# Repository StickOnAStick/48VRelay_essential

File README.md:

Ignore me trying to work with ki-cads git management. Project is located at `RelatBoard/48VRelay/48VERelay`

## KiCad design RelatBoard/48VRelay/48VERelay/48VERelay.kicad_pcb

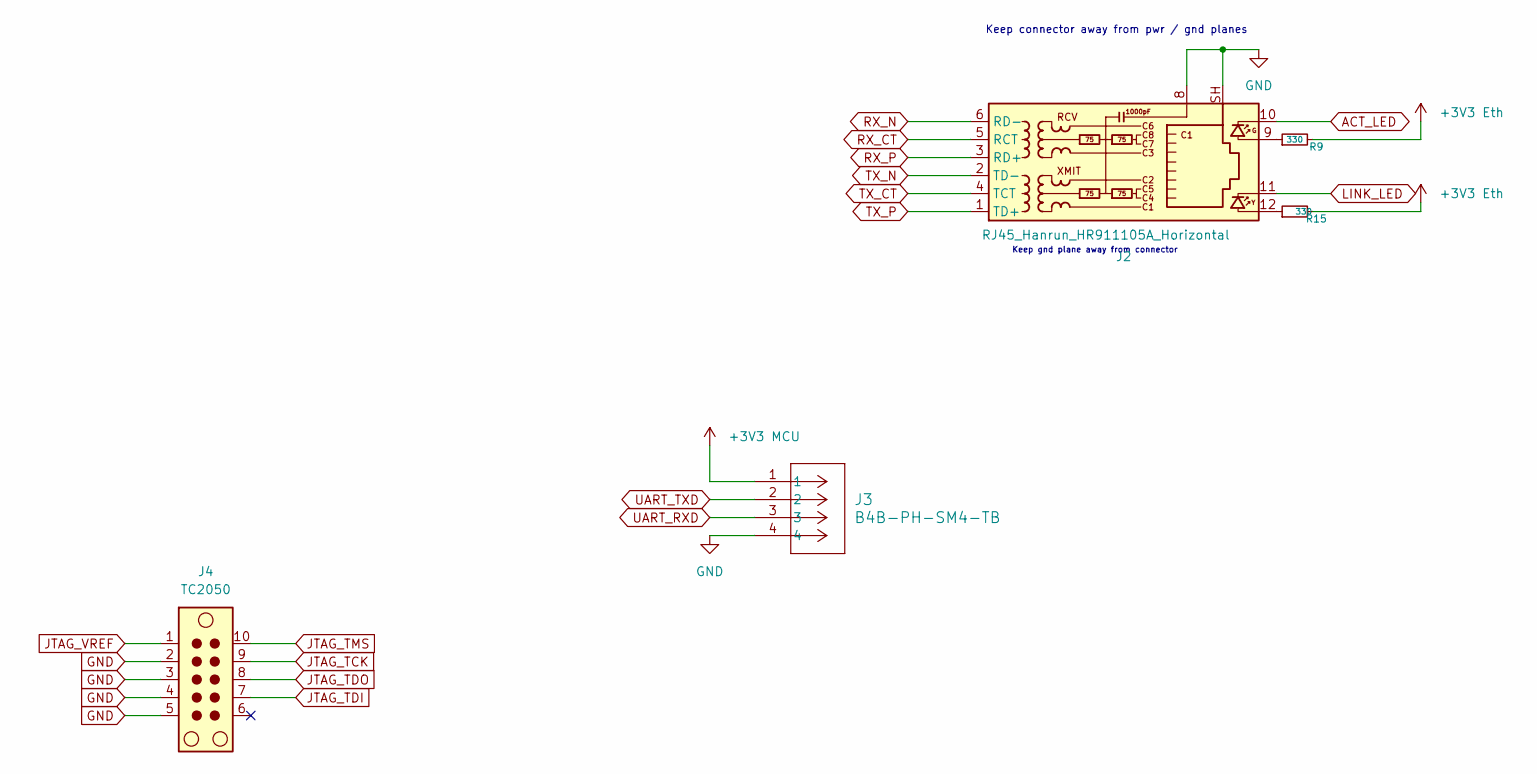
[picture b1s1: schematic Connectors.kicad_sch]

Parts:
J2: RJ45_Hanrun_HR911105A_Horizontal
J3: B4B-PH-SM4-TB; PinHeader_1x04_P2.54mm_Vertical
J4: TC2050; Tag-Connect_TC2050-IDC-NL_2x05_P1.27mm_Vertical
R9, R15: 330; R_0603_1608Metric

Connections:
3V3 MCU: J3.1, J4.1; also elsewhere on the board
+3V3 Eth: R9.2, R15.2; also elsewhere on the board
ACT_LED: J2.10; also elsewhere on the board
GND: J2.8, J2.SH, J3.4, J4.2, J4.3, J4.4, J4.5; also elsewhere on the board
JTAG_TCK: J4.9; also elsewhere on the board
JTAG_TDI: J4.7; also elsewhere on the board
JTAG_TDO: J4.8; also elsewhere on the board
JTAG_TMS: J4.10; also elsewhere on the board
LINK_LED: J2.11; also elsewhere on the board
unnamed: J2.9, R9.1
unnamed: J2.12, R15.1
RX_CT: J2.5 (RCT); also elsewhere on the board
RX_N: J2.6 (RD-); also elsewhere on the board
RX_P: J2.3 (RD+); also elsewhere on the board
TX_CT: J2.4 (TCT); also elsewhere on the board
TX_N: J2.2 (TD-); also elsewhere on the board
TX_P: J2.1 (TD+); also elsewhere on the board
UART_RXD: J3.3; also elsewhere on the board
UART_TXD: J3.2; also elsewhere on the board

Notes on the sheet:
Keep gnd plane away from connector
Keep connector away from pwr / gnd planes

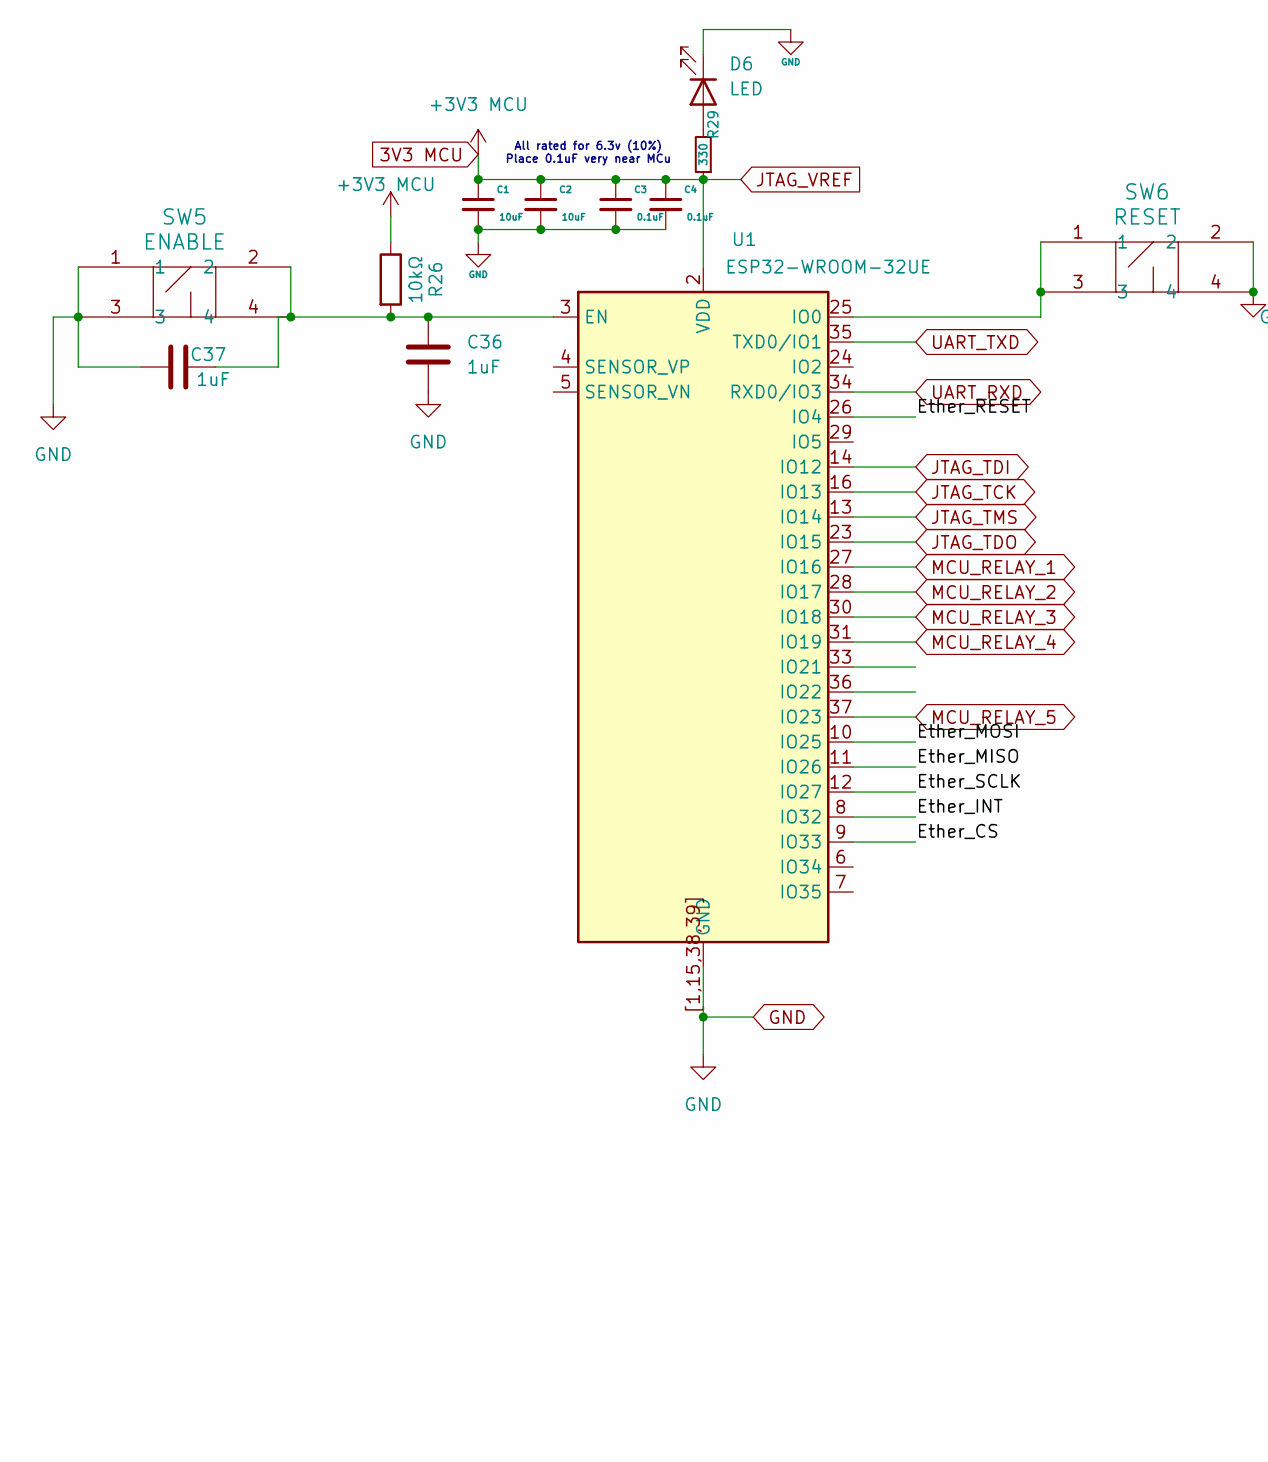
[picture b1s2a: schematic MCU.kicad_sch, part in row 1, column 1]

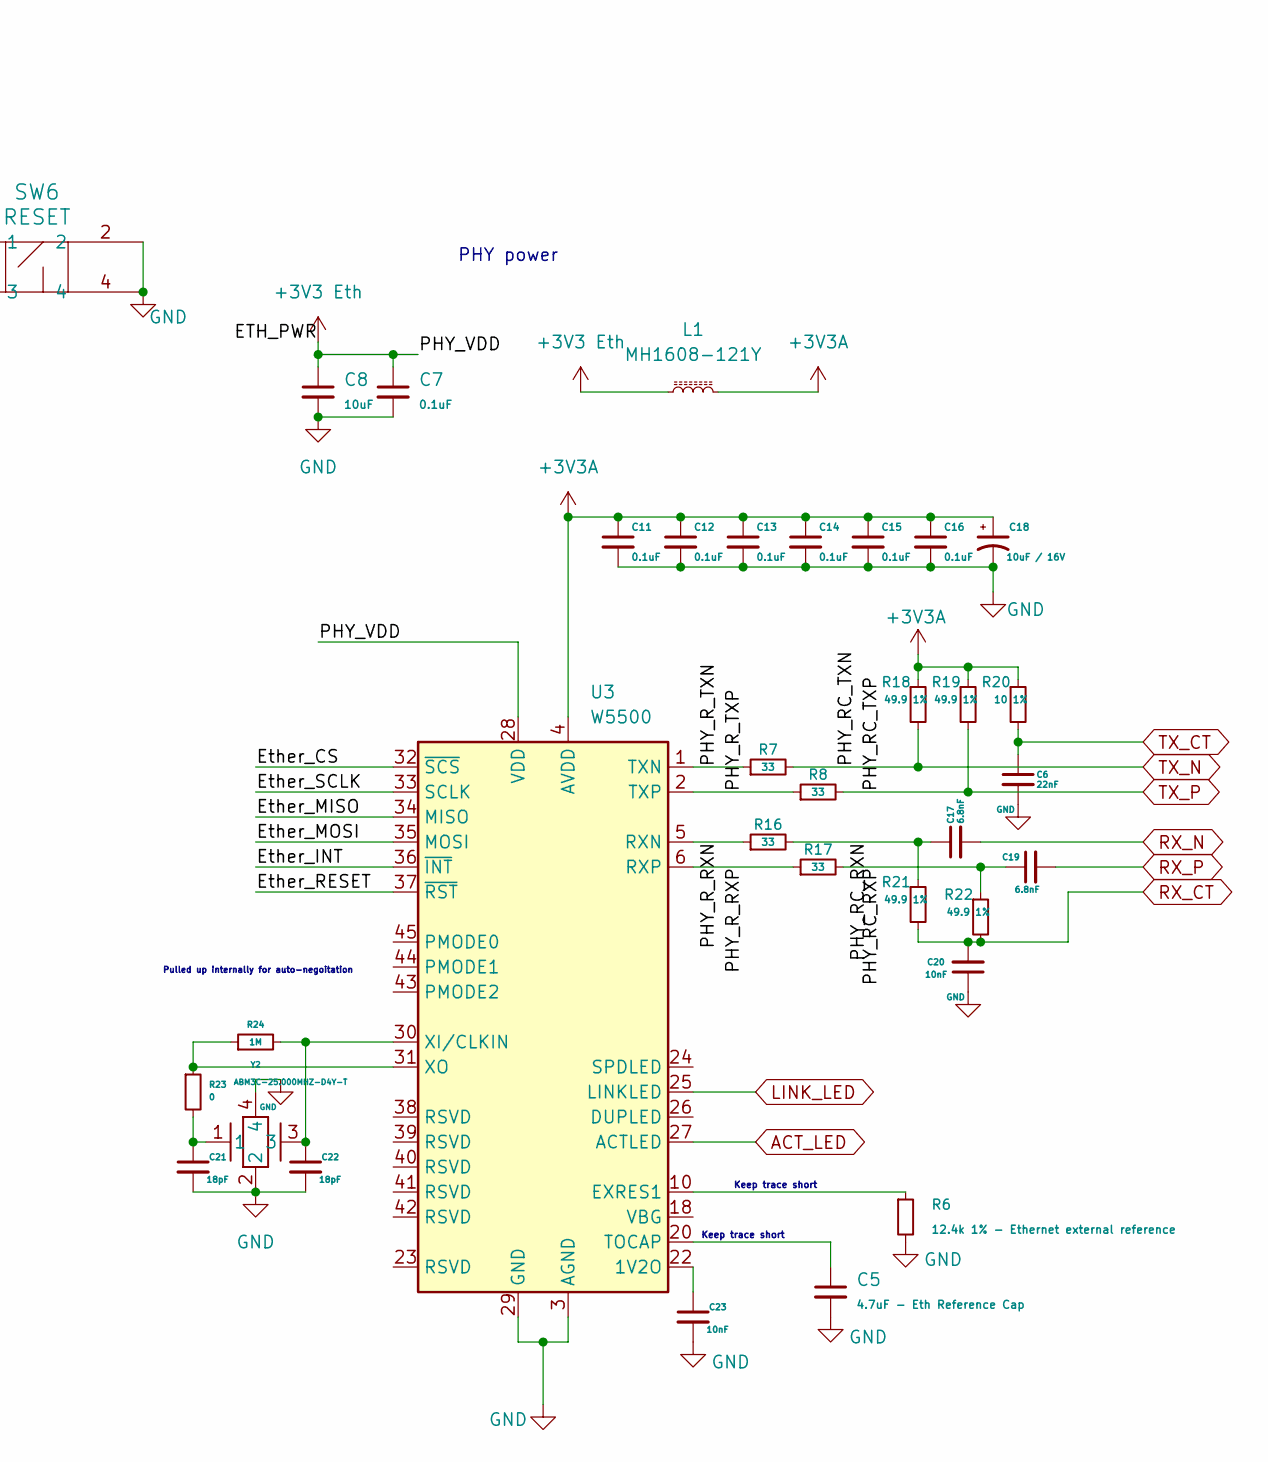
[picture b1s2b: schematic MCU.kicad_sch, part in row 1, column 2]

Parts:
C1, C8: 10uF; C_0805_2012Metric
C2: 10uF; C_0603_1608Metric
C3, C4: 0.1uF; C_0603_1608Metric
C5: 4.7uF - Eth Reference Cap; C_0201_0603Metric
C6: 22nF; C_0201_0603Metric
C7: 0.1uF; C_0201_0603Metric
C11, C12, C13, C14, C15, C16: 0.1uF; C_0402_1005Metric
C17, C19: 6.8nF; C_0201_0603Metric
C18: 10uF / 16V; C_0805_2012Metric
C20, C23: 10nF; C_0201_0603Metric
C21, C22: 18pF; C_0201_0603Metric
C36, C37: 1uF; C_0402_1005Metric
D6: LED; LED_0603_1608Metric
L1: MH1608-121Y; IND_BOURNS_MH1608
R6: 12.4k 1% - Ethernet external reference; R_0402_1005Metric
R7, R8, R16, R17: 33; R_0603_1608Metric
R18, R19, R21, R22: 49.9 1%; R_0201_0603Metric
R20: 10 1%; R_0201_0603Metric
R23: 0; R_0402_1005Metric
R24: 1M; R_0402_1005Metric
R26: 10kΩ; R_0402_1005Metric
R29: 330; R_0603_1608Metric
SW5: ENABLE; SW_PUSH_6mm_H5mm
SW6: RESET; SW_PUSH_6mm_H5mm
U1: ESP32-WROOM-32UE
U3: W5500; LQFP-48_7x7mm_P0.5mm
Y2: ABM3C-25.000MHZ-D4Y-T; CRYSTAL_ABM3C_ABR-M

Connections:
3V3 MCU: C1.1, C2.1, C3.1, C4.1, R26.1, R29.1, U1.2 (VDD); also elsewhere on the board
+3V3 Eth: C7.1, C8.1, L1.1, U3.28 (VDD); also elsewhere on the board
+3V3A: C11.1, C12.1, C13.1, C14.1, C15.1, C16.1, C18.1, L1.2, R18.1, R19.1, R20.1, U3.4 (AVDD), U3.8 (AVDD), U3.11 (AVDD), U3.15 (AVDD), U3.17 (AVDD), U3.21 (AVDD); also elsewhere on the board
/MCU/Ether_CS: U1.9 (IO33), U3.32 (~SCS)
/MCU/Ether_INT: U1.8 (IO32), U3.36 (~INT)
/MCU/Ether_MISO: U1.11 (IO26), U3.34 (MISO)
/MCU/Ether_MOSI: U1.10 (IO25), U3.35 (MOSI)
/MCU/Ether_RESET: U1.26 (IO4), U3.37 (~RST)
/MCU/Ether_SCLK: U1.12 (IO27), U3.33 (SCLK)
/MCU/PHY_RC_RXN: C17.1, R16.2, R21.1
/MCU/PHY_RC_RXP: C19.1, R17.2, R22.1
/MCU/PHY_R_RXN: R16.1, U3.5 (RXN)
/MCU/PHY_R_RXP: R17.1, U3.6 (RXP)
/MCU/PHY_R_TXN: R7.1, U3.1 (TXN)
/MCU/PHY_R_TXP: R8.1, U3.2 (TXP)
ACT_LED: U3.27 (ACTLED); also elsewhere on the board
GND: C1.2, C2.2, C3.2, C4.2, C5.2, C6.2, C7.2, C8.2, C11.2, C12.2, C13.2, C14.2, C15.2, C16.2, C18.2, C20.1, C21.2, C22.2, C23.2, C36.2, C37.2, D6.1 (K), R6.2, SW5.1, SW5.3, SW6.2, SW6.4, U1.1 (GND), U1.15 (GND), U1.38 (GND), U1.39 (GND), U1.[1,15,38,39] (GND), U3.3 (AGND), U3.9 (AGND), U3.14 (AGND), U3.16 (AGND), U3.19 (AGND), U3.29 (GND), U3.48 (AGND), Y2.2, Y2.4; also elsewhere on the board
JTAG_TCK: U1.16 (IO13); also elsewhere on the board
JTAG_TDI: U1.14 (IO12); also elsewhere on the board
JTAG_TDO: U1.23 (IO15); also elsewhere on the board
JTAG_TMS: U1.13 (IO14); also elsewhere on the board
LINK_LED: U3.25 (LINKLED); also elsewhere on the board
MCU_RELAY_1: U1.27 (IO16); also elsewhere on the board
MCU_RELAY_2: U1.28 (IO17); also elsewhere on the board
MCU_RELAY_3: U1.30 (IO18); also elsewhere on the board
MCU_RELAY_4: U1.31 (IO19); also elsewhere on the board
MCU_RELAY_5: U1.37 (IO23); also elsewhere on the board
unnamed: C21.1, R23.2, Y2.1
unnamed: D6.2 (A), R29.2
unnamed: C36.1, C37.1, R26.2, SW5.2, SW5.4, U1.3 (EN)
unnamed: SW6.1, SW6.3, U1.25 (IO0)
unnamed: C23.1, U3.22 (1V2O)
unnamed: R6.1, U3.10 (EXRES1)
unnamed: C5.1, U3.20 (TOCAP)
unnamed: C22.1, R24.2, U3.30 (XI/CLKIN), Y2.3
unnamed: R23.1, R24.1, U3.31 (XO)
RX_CT: C20.2, R21.2, R22.2; also elsewhere on the board
RX_N: C17.2; also elsewhere on the board
RX_P: C19.2; also elsewhere on the board
TX_CT: C6.1, R20.2; also elsewhere on the board
TX_N: R7.2, R18.2; also elsewhere on the board
TX_P: R8.2, R19.2; also elsewhere on the board
UART_RXD: U1.34 (RXD0/IO3); also elsewhere on the board
UART_TXD: U1.35 (TXD0/IO1); also elsewhere on the board

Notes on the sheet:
Keep trace short
PHY power
All rated for 6.3v (10%) Place 0.1uF very near MCu
Pulled up internally for auto-negoitation

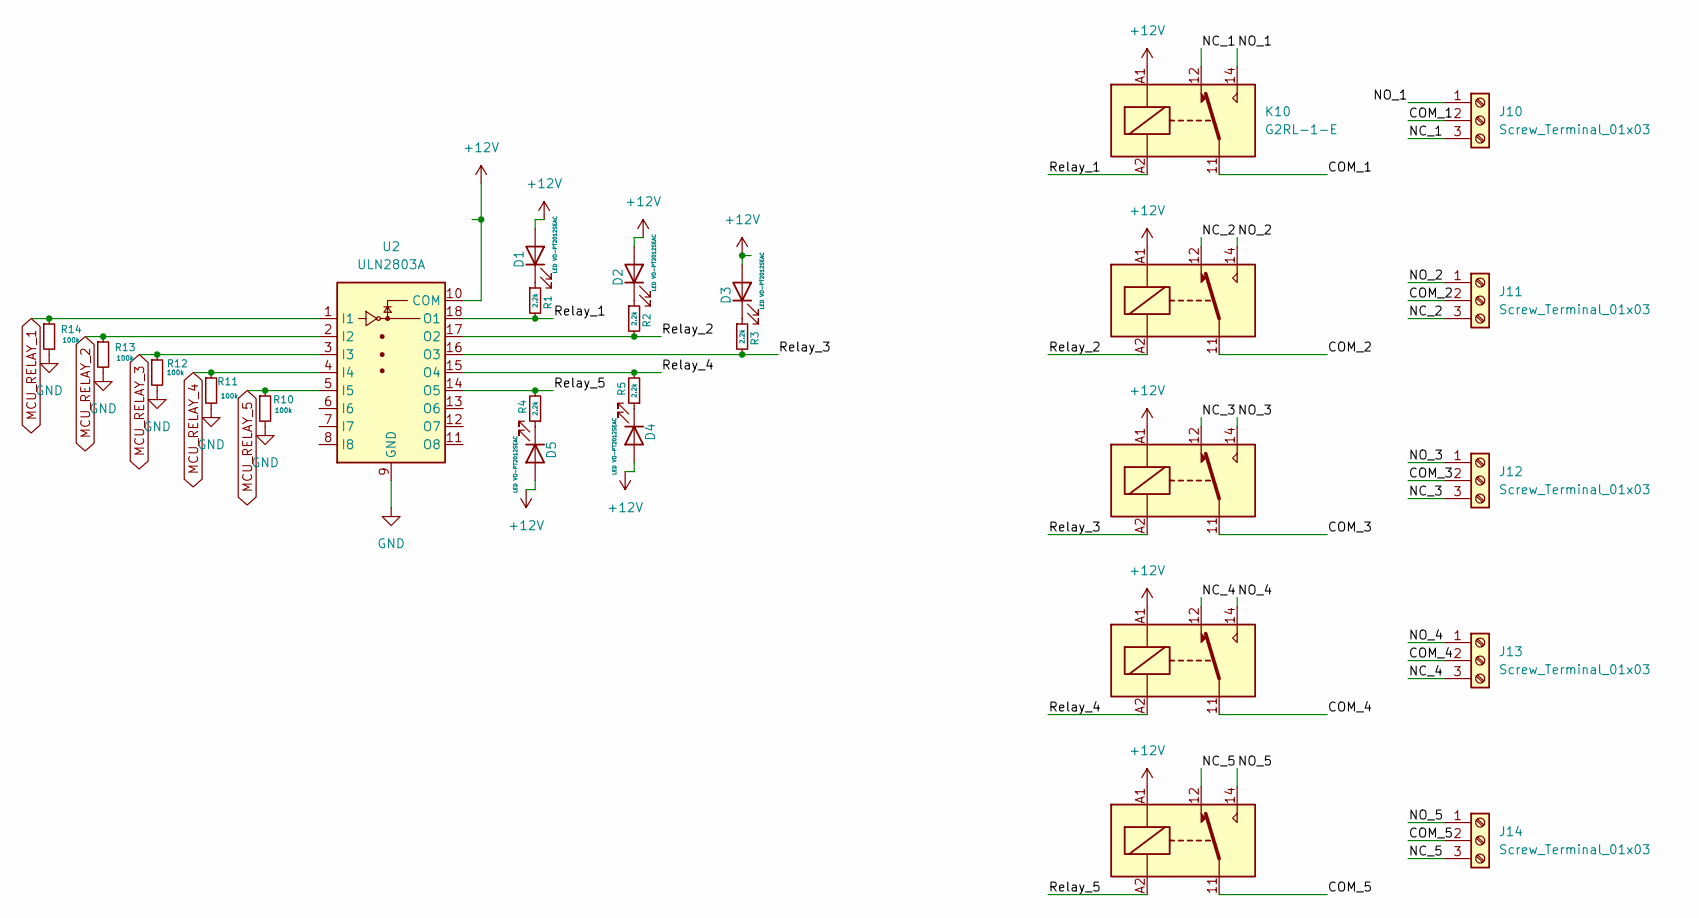
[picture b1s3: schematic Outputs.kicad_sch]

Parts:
D1, D2, D3, D4, D5: LED VO-PT2012SEAC; LED_0805_2012Metric
J10, J11, J12, J13, J14: Screw_Terminal_01x03; TerminalBlock_MaiXu_MX126-5.0-03P_1x03_P5.00mm
K10, K11, K12, K13, K14: G2RL-1-E; Relay_SPDT_Omron_G2RL-1-E
R1, R2, R3, R4, R5: 2.2k; R_0603_1608Metric
R10, R11, R12, R13, R14: 100k; R_0603_1608Metric
U2: ULN2803A; SOIC-18W_7.5x11.6mm_P1.27mm

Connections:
+12V: D1.2 (A), D2.2 (A), D3.2 (A), D4.2 (A), D5.2 (A), K10.A1, K11.A1, K12.A1, K13.A1, K14.A1, U2.10 (COM); also elsewhere on the board
/Outputs/COM_1: J10.2, K10.11
/Outputs/COM_2: J11.2, K11.11
/Outputs/COM_3: J12.2, K12.11
/Outputs/COM_4: J13.2, K13.11
/Outputs/COM_5: J14.2, K14.11
/Outputs/NC_1: J10.3, K10.12
/Outputs/NC_2: J11.3, K11.12
/Outputs/NC_3: J12.3, K12.12
/Outputs/NC_4: J13.3, K13.12
/Outputs/NC_5: J14.3, K14.12
/Outputs/NO_1: J10.1, K10.14
/Outputs/NO_2: J11.1, K11.14
/Outputs/NO_3: J12.1, K12.14
/Outputs/NO_4: J13.1, K13.14
/Outputs/NO_5: J14.1, K14.14
/Outputs/Relay_1: K10.A2, R1.2, U2.18 (O1)
/Outputs/Relay_2: K11.A2, R2.2, U2.17 (O2)
/Outputs/Relay_3: K12.A2, R3.2, U2.16 (O3)
/Outputs/Relay_4: K13.A2, R5.2, U2.15 (O4)
/Outputs/Relay_5: K14.A2, R4.2, U2.14 (O5)
GND: R10.2, R11.2, R12.2, R13.2, R14.2, U2.9 (GND); also elsewhere on the board
MCU_RELAY_1: R14.1, U2.1 (I1); also elsewhere on the board
MCU_RELAY_2: R13.1, U2.2 (I2); also elsewhere on the board
MCU_RELAY_3: R12.1, U2.3 (I3); also elsewhere on the board
MCU_RELAY_4: R11.1, U2.4 (I4); also elsewhere on the board
MCU_RELAY_5: R10.1, U2.5 (I5); also elsewhere on the board
unnamed: D1.1 (K), R1.1
unnamed: D2.1 (K), R2.1
unnamed: D3.1 (K), R3.1
unnamed: D4.1 (K), R5.1
unnamed: D5.1 (K), R4.1

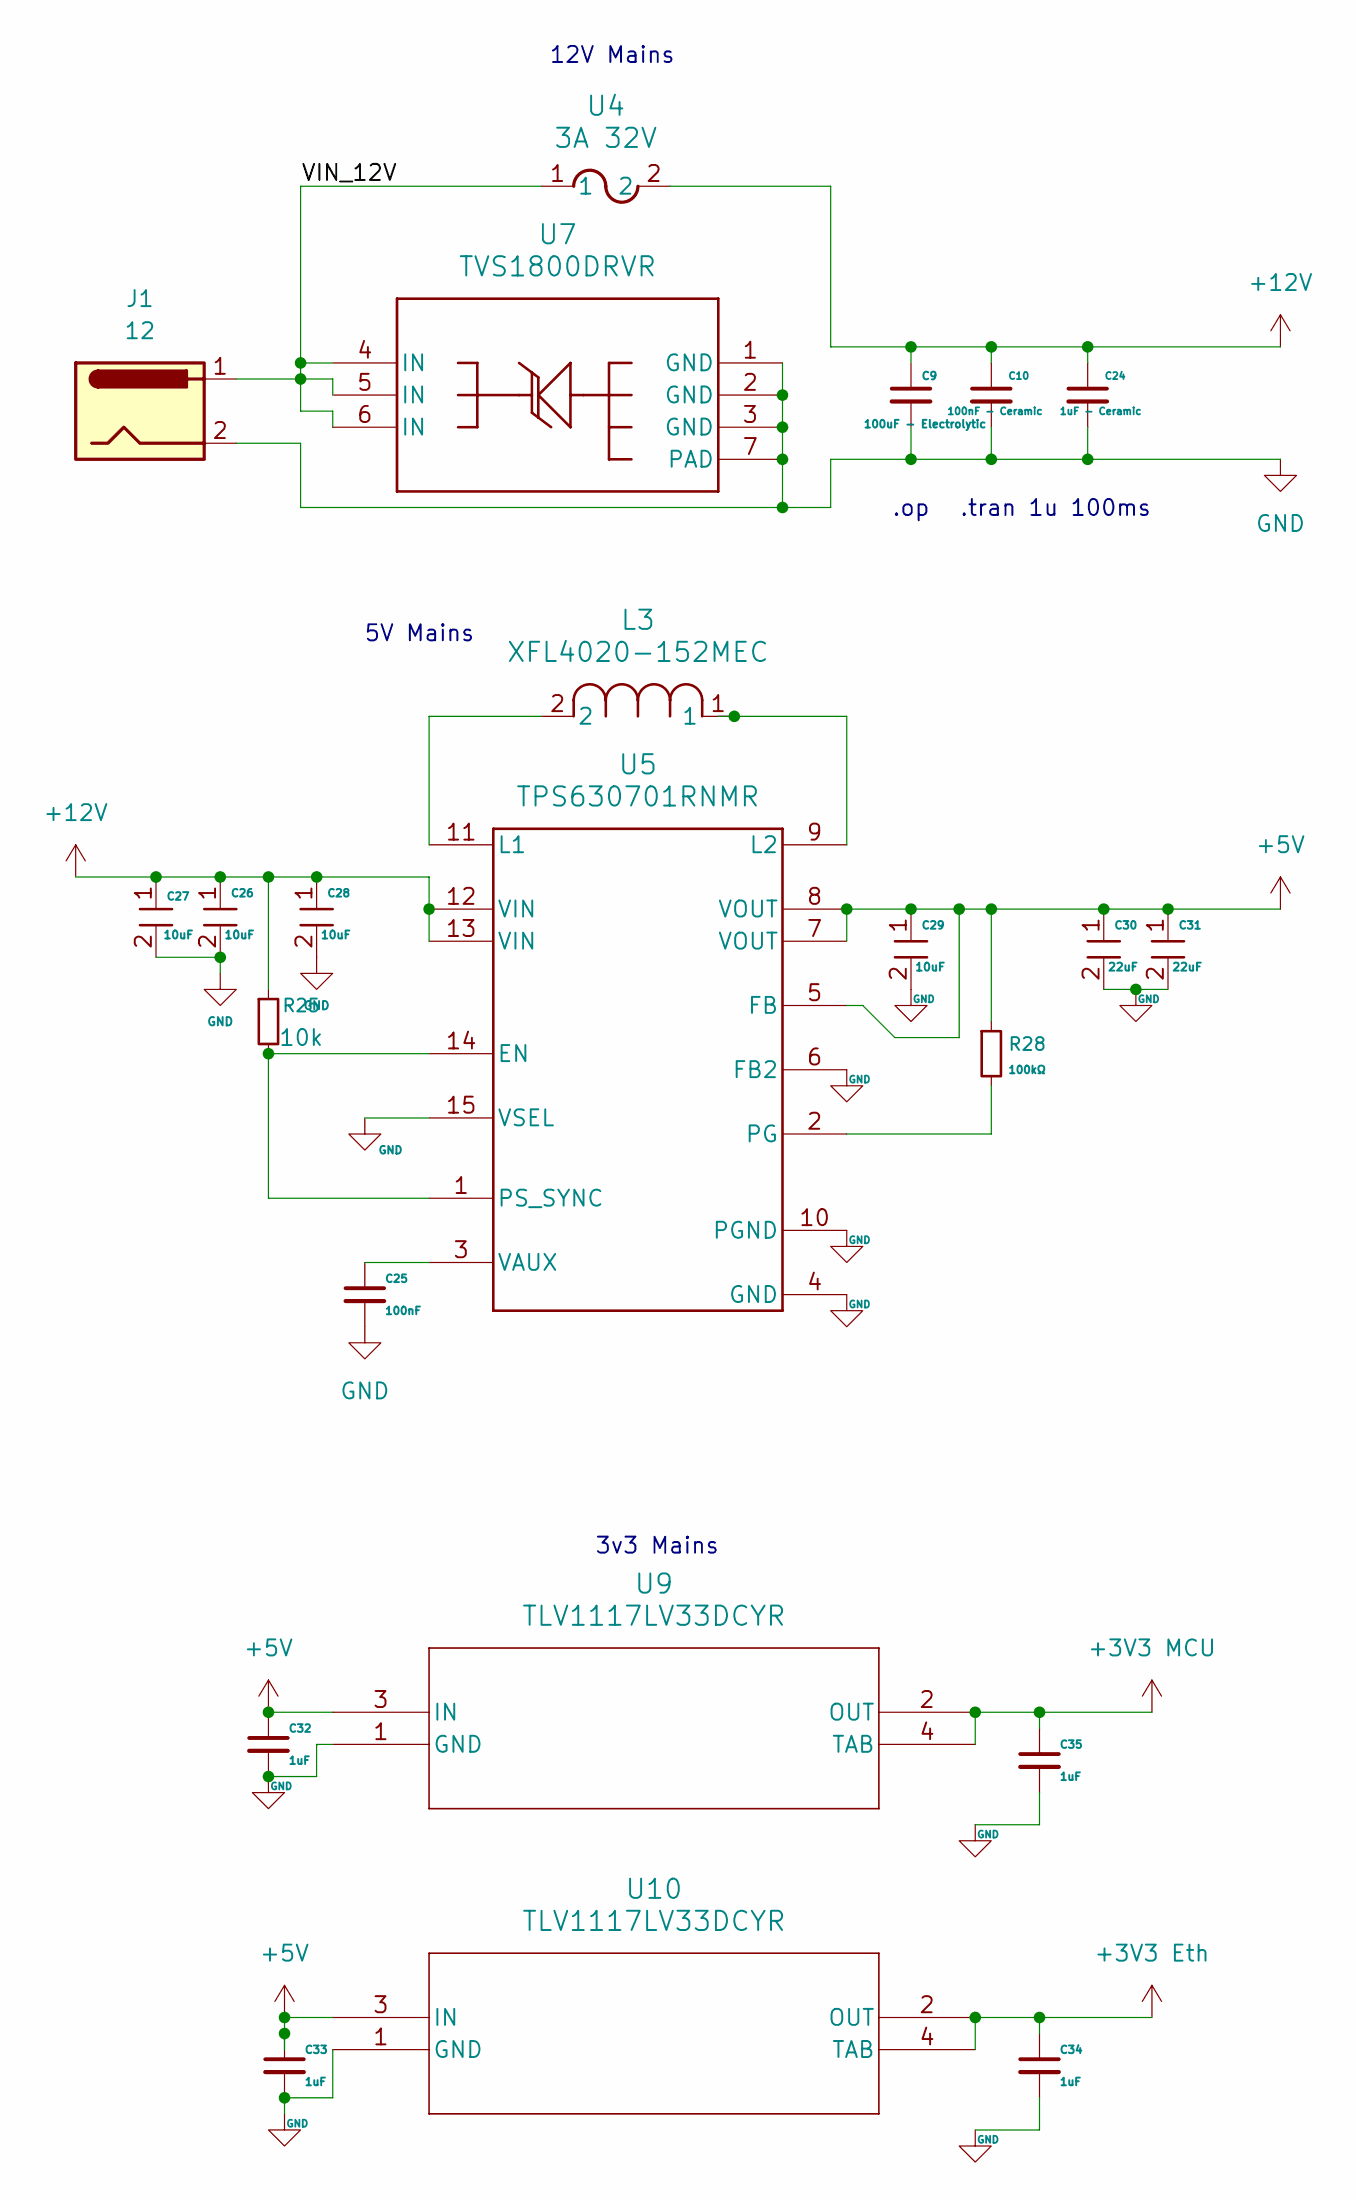
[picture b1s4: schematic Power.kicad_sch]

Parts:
C9: 100uF - Electrolytic; C_Elec_6.3x7.7
C10: 100nF - Ceramic; C_0603_1608Metric
C24: 1uF - Ceramic; C_0805_2012Metric
C25: 100nF; C_0201_0603Metric
C26, C27: 10uF; C_0805_2012Metric
C28, C29: 10uF; C_0603_1608Metric
C30, C31: 22uF; C_0805_2012Metric
C32, C33, C34, C35: 1uF; C_0805_2012Metric
J1: 12; BarrelJack_CUI_PJ-102AH_Horizontal
L3: XFL4020-152MEC; IND_XFL4020_COC-M
R25: 10k; R_0603_1608Metric
R28: 100kΩ; R_0603_1608Metric
U4: 3A 32V; Fuse_1206_3216Metric
U5: TPS630701RNMR; RNM0015A
U7: TVS1800DRVR; DRV0006A_NV
U9, U10: TLV1117LV33DCYR; TLV1117-33IDCYR

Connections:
3V3 MCU: C35.1, U9.2 (OUT), U9.4 (TAB); also elsewhere on the board
+3V3 Eth: C34.1, U10.2 (OUT), U10.4 (TAB); also elsewhere on the board
+5V: C29.1, C30.1, C31.1, C32.1, C33.1, R28.1, U5.5 (FB), U5.7 (VOUT), U5.8 (VOUT), U9.3 (IN), U10.3 (IN); also elsewhere on the board
+12V: C9.1, C10.1, C24.1, C26.1, C27.1, C28.1, R25.1, U4.2, U5.12 (VIN), U5.13 (VIN); also elsewhere on the board
/Power/VIN_12V: J1.1, U4.1, U7.4 (IN), U7.5 (IN), U7.6 (IN)
GND: C9.2, C10.2, C24.2, C25.2, C26.2, C27.2, C28.2, C29.2, C30.2, C31.2, C32.2, C33.2, C34.2, C35.2, J1.2, U5.4 (GND), U5.6 (FB2), U5.10 (PGND), U5.15 (VSEL), U7.1 (GND), U7.2 (GND), U7.3 (GND), U7.7 (PAD), U9.1 (GND), U10.1 (GND); also elsewhere on the board
unnamed: R25.2, U5.1 (PS_SYNC), U5.14 (EN)
unnamed: L3.2, U5.11 (L1)
unnamed: L3.1, U5.9 (L2)
unnamed: R28.2, U5.2 (PG)
unnamed: C25.1, U5.3 (VAUX)

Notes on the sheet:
3v3 Mains
12V Mains
5V Mains
.tran 1u 100ms
.op

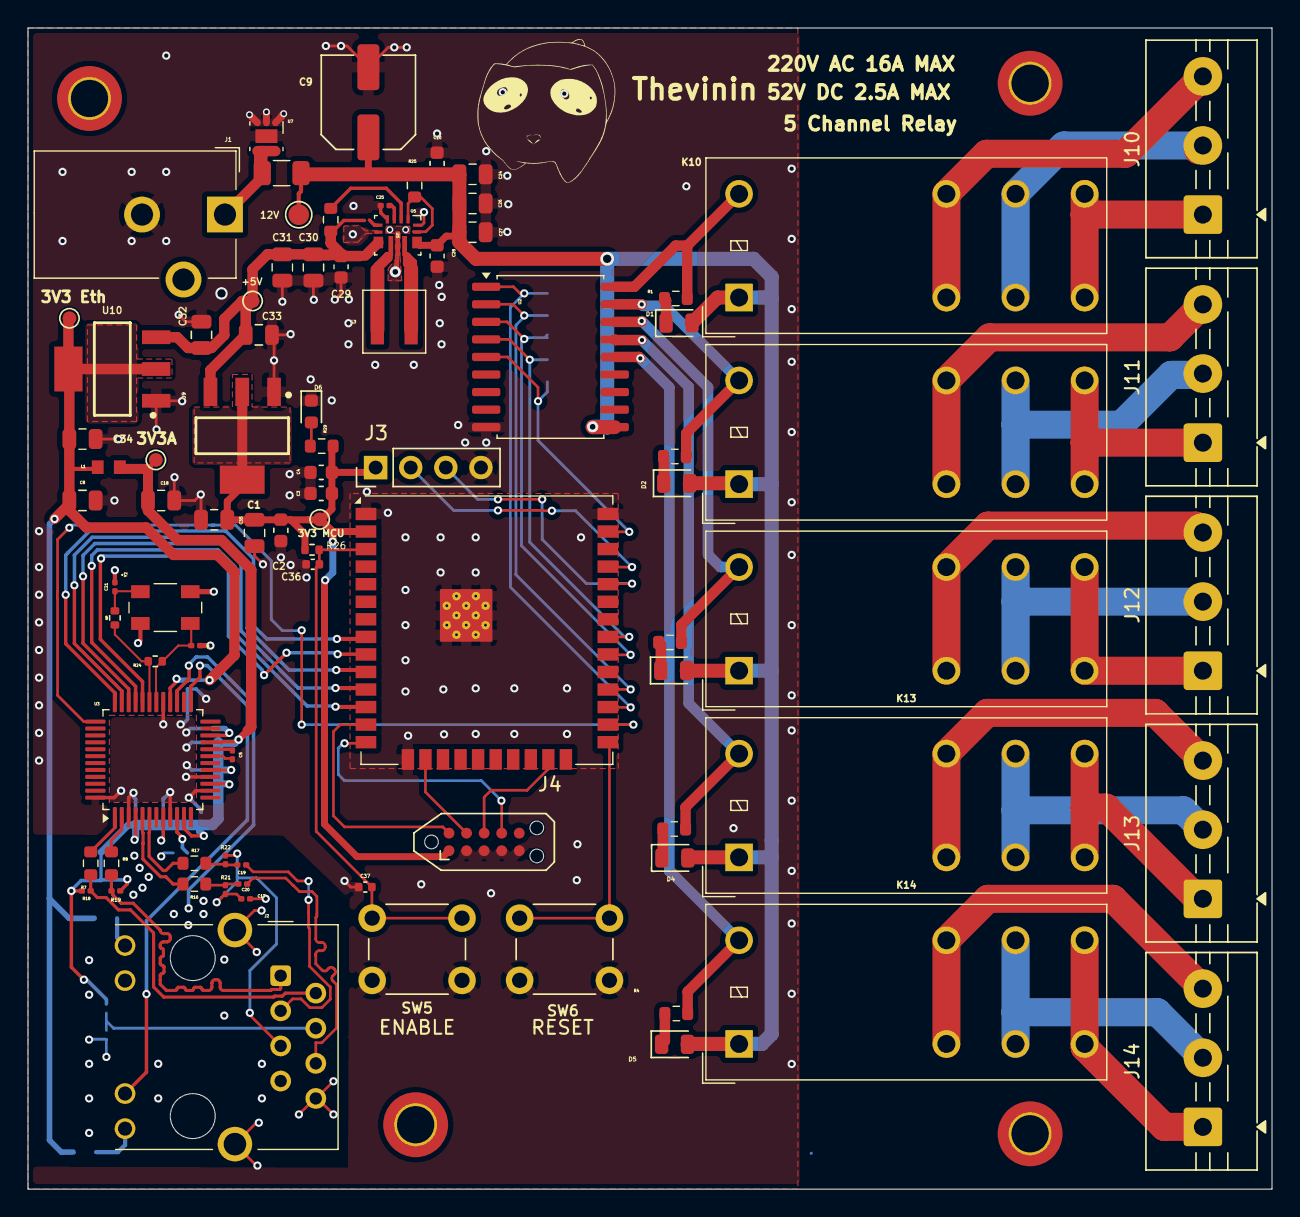
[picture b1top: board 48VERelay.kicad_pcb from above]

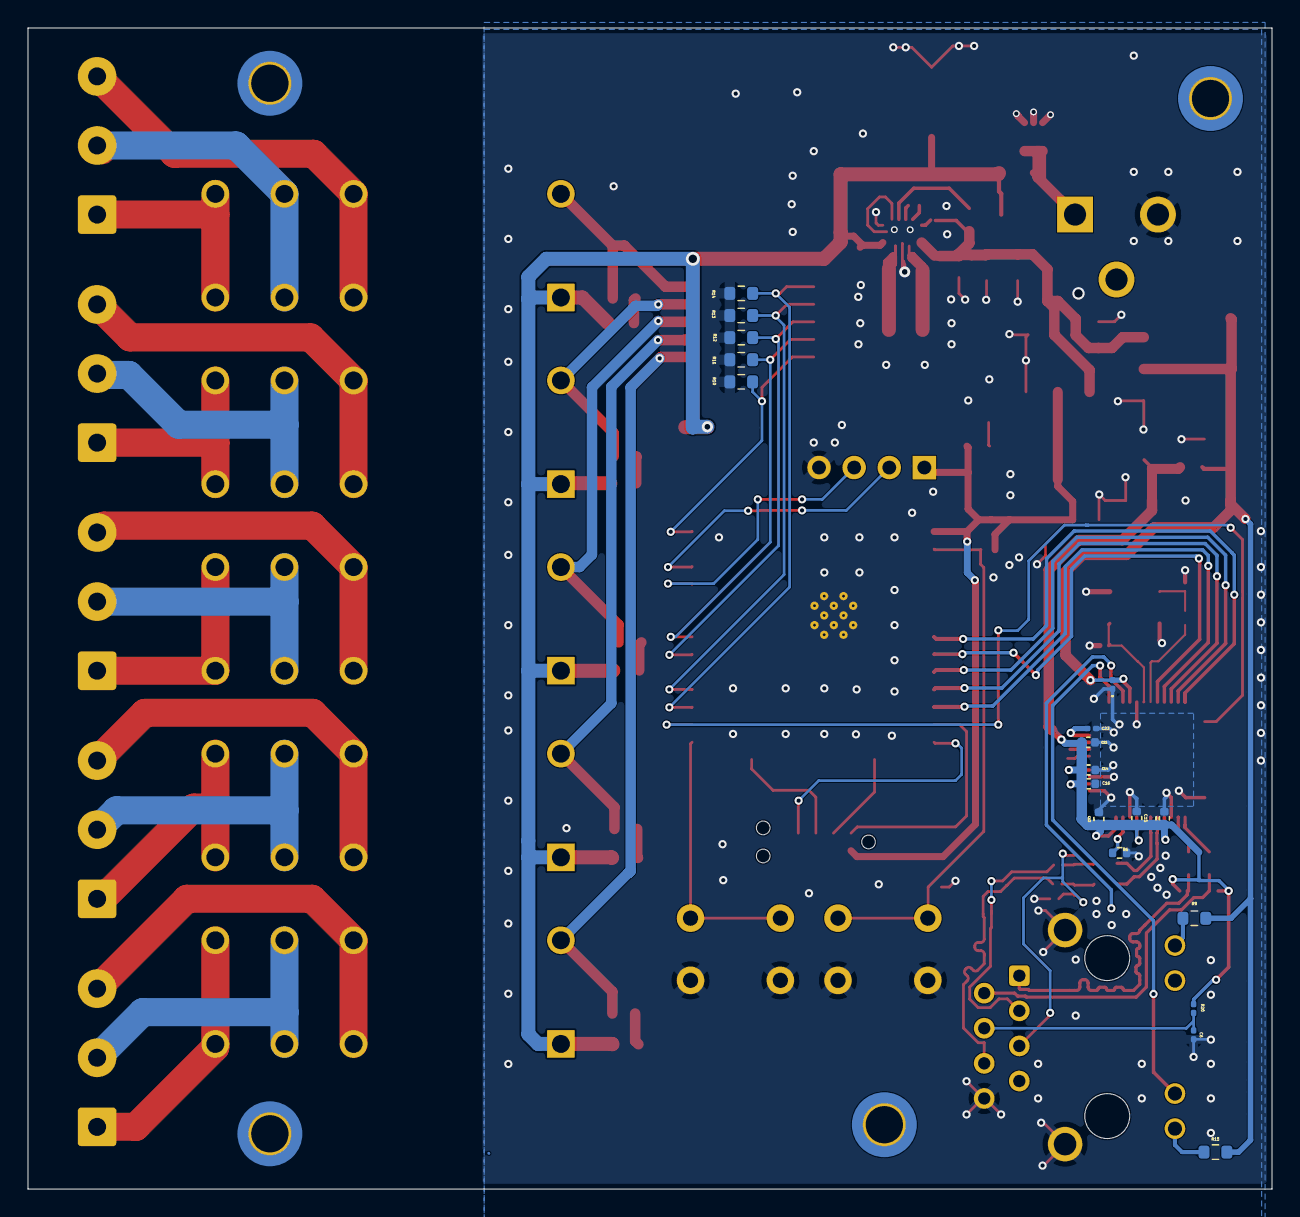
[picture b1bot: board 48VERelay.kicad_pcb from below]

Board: 4 copper layers, 90.0 x 84.0 mm, 103 parts (18 on the bottom side), 79 nets.

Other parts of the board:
3V3 Eth, 3V3 MCU, 3V3A: TestPoint_Pad_D1.0mm
12V: TestPoint_Pad_D1.5mm
+5V: TestPoint_Pad_D1.0mm

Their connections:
3V3 MCU: 3V3 MCU.1; also elsewhere on the board
+3V3 Eth: 3V3 Eth.1; also elsewhere on the board
+3V3A: 3V3A.1; also elsewhere on the board
+5V: +5V.1; also elsewhere on the board
+12V: 12V.1; also elsewhere on the board

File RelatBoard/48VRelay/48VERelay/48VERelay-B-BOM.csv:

"Id";"Designator";"Footprint";"Quantity";"Designation";"Supplier and ref";
1;"C1, C8, C26, C27";"C_0805_2012Metric";4;"10uF";;;
2;"C2, C28, C29";"C_0603_1608Metric";3;"10uF";;;
3;"C3, C4";"C_0603_1608Metric";2;"0.1uF";;;
4;"C5";"C_0201_0603Metric";1;"4.7uF - Eth Reference Cap";;;
5;"C6";"C_0201_0603Metric";1;"22nF";;;
6;"C7";"C_0201_0603Metric";1;"0.1uF";;;
7;"C9";"C_Elec_6.3x7.7";1;"100uF - Electrolytic";;;
8;"C10";"C_0603_1608Metric";1;"100nF - Ceramic";;;
9;"C11, C12, C13, C14, C15, C16";"C_0402_1005Metric";6;"0.1uF";;;
10;"C17, C19";"C_0201_0603Metric";2;"6.8nF";;;
11;"C18";"C_0805_2012Metric";1;"10uF / 16V";;;
12;"C20, C23";"C_0201_0603Metric";2;"10nF";;;
13;"C21, C22";"C_0201_0603Metric";2;"18pF";;;
14;"C24";"C_0805_2012Metric";1;"1uF - Ceramic";;;
15;"C25";"C_0201_0603Metric";1;"100nF";;;
16;"C30, C31";"C_0805_2012Metric";2;"22uF";;;
17;"C32, C33, C34, C35";"C_0805_2012Metric";4;"1uF";;;
18;"C36, C37";"C_0402_1005Metric";2;"1uF";;;
19;"D1, D2, D3, D4, D5";"LED_0805_2012Metric";5;"LED VO-PT2012SEAC";;;
20;"D6";"LED_0603_1608Metric";1;"LED";;;
21;"J1";"BarrelJack_CUI_PJ-102AH_Horizontal";1;"12";;;
22;"J2";"RJ45_Hanrun_HR911105A_Horizontal";1;"RJ45_Hanrun_HR911105A_Horizontal";;;
23;"J3";"PinHeader_1x04_P2.54mm_Vertical";1;"B4B-PH-SM4-TB";;;
24;"J10, J11, J12, J13, J14";"TerminalBlock_MaiXu_MX126-5.0-03P_1x03_P5.00mm";5;"Screw_Terminal_01x03";;;
25;"K10, K11, K12, K13, K14";"Relay_SPDT_Omron_G2RL-1-E";5;"G2RL-1-E";;;
26;"L1";"IND_BOURNS_MH1608";1;"MH1608-121Y";;;
27;"L3";"IND_XFL4020_COC-M";1;"XFL4020-152MEC";;;
28;"R1, R2, R3, R4, R5";"R_0603_1608Metric";5;"2.2k";;;
29;"R6";"R_0402_1005Metric";1;"12.4k 1% - Ethernet external reference";;;
30;"R7, R8, R16, R17";"R_0603_1608Metric";4;"33";;;
31;"R9, R15, R29";"R_0603_1608Metric";3;"330";;;
32;"R10, R11, R12, R13, R14";"R_0603_1608Metric";5;"100k";;;
33;"R18, R19, R21, R22";"R_0201_0603Metric";4;"49.9 1%";;;
34;"R20";"R_0201_0603Metric";1;"10 1%";;;
35;"R23";"R_0402_1005Metric";1;"0";;;
36;"R24";"R_0402_1005Metric";1;"1M";;;
37;"R25";"R_0603_1608Metric";1;"10k";;;
38;"R26";"R_0402_1005Metric";1;"10kΩ";;;
39;"R28";"R_0603_1608Metric";1;"100kΩ";;;
40;"SW5";"SW_PUSH_6mm_H5mm";1;"ENABLE";;;
41;"SW6";"SW_PUSH_6mm_H5mm";1;"RESET";;;
42;"U1";"ESP32-WROOM-32UE";1;"ESP32-WROOM-32UE";;;
43;"U2";"SOIC-18W_7.5x11.6mm_P1.27mm";1;"ULN2803A";;;
44;"U3";"LQFP-48_7x7mm_P0.5mm";1;"W5500";;;
45;"U4";"Fuse_1206_3216Metric";1;"3A 32V";;;
46;"U5";"RNM0015A";1;"TPS630701RNMR";;;
47;"U7";"DRV0006A_NV";1;"TVS1800DRVR";;;
48;"U9, U10";"TLV1117-33IDCYR";2;"TLV1117LV33DCYR";;;
49;"Y2";"CRYSTAL_ABM3C_ABR-M";1;"ABM3C-25.000MHZ-D4Y-T";;;

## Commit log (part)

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2026-06-15 Start Sim
2026-06-15 sys_update
2026-06-17 begin pcb design
2026-06-22 Begin PCB layout
2026-06-27 5v5 Buck Added
2026-06-29 Fix 12V->5V add power plane
